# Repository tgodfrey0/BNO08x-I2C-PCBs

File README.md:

# BNO085 Interface Boards (I2C)

This repository contains W.I.P. code and hardware designed for a 9DOF sensor module using a BNO085.

The [`hardware` folder](hardware/README.md) contains all KiCAD files for the board.

The [`firmware` folder](firmware/README.md) contains the files required to run the sensor.

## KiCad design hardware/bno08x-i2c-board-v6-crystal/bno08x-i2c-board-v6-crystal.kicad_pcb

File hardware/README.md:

# Hardware

The PCB designs were created in KiCAD and the panels were made using KiKit.

The sensor board is designed to be as small as possible, for this reason some features of the BNO085 are no longer accessible.

## PCB Board Key

Some of the boards are keyed to give them a known orientation. 

Both keys was created from the insersection between the main PCB edge circle and another circle placed in the top right corner of the main circle's bounding box. They are outlined below in the relevant screenshots (the y-axis has been inverted in Geogebra to visually match the KiCAD coordinate system).

### v6

All v6 boards have the same key and same key location. This is a through-hole with a diameter of 1mm. The centre of the key hole is located in the top left corner of the board; -3.35mm from the centre of the board along the x-axis, -3.25mm from the centre of the board along the y-axis. For both board sizes the hole is located in the same place. (Remember the KiCAD y-axis is inverted, therefore the delta-y of -3.25 means the hole is above the centre of the board.) 

### v5

The v5 board design has no physical key, however orientation pads were added to the front and back silkscreen these are in the top-left, top-right and bottom-right corners and can be used to orientate the board.

### v3

### v3-base

This board is the base for the `v3` panel. The difference is the flat spots by each pin to allow it to be panelised. This means the dimensions are slightly different.

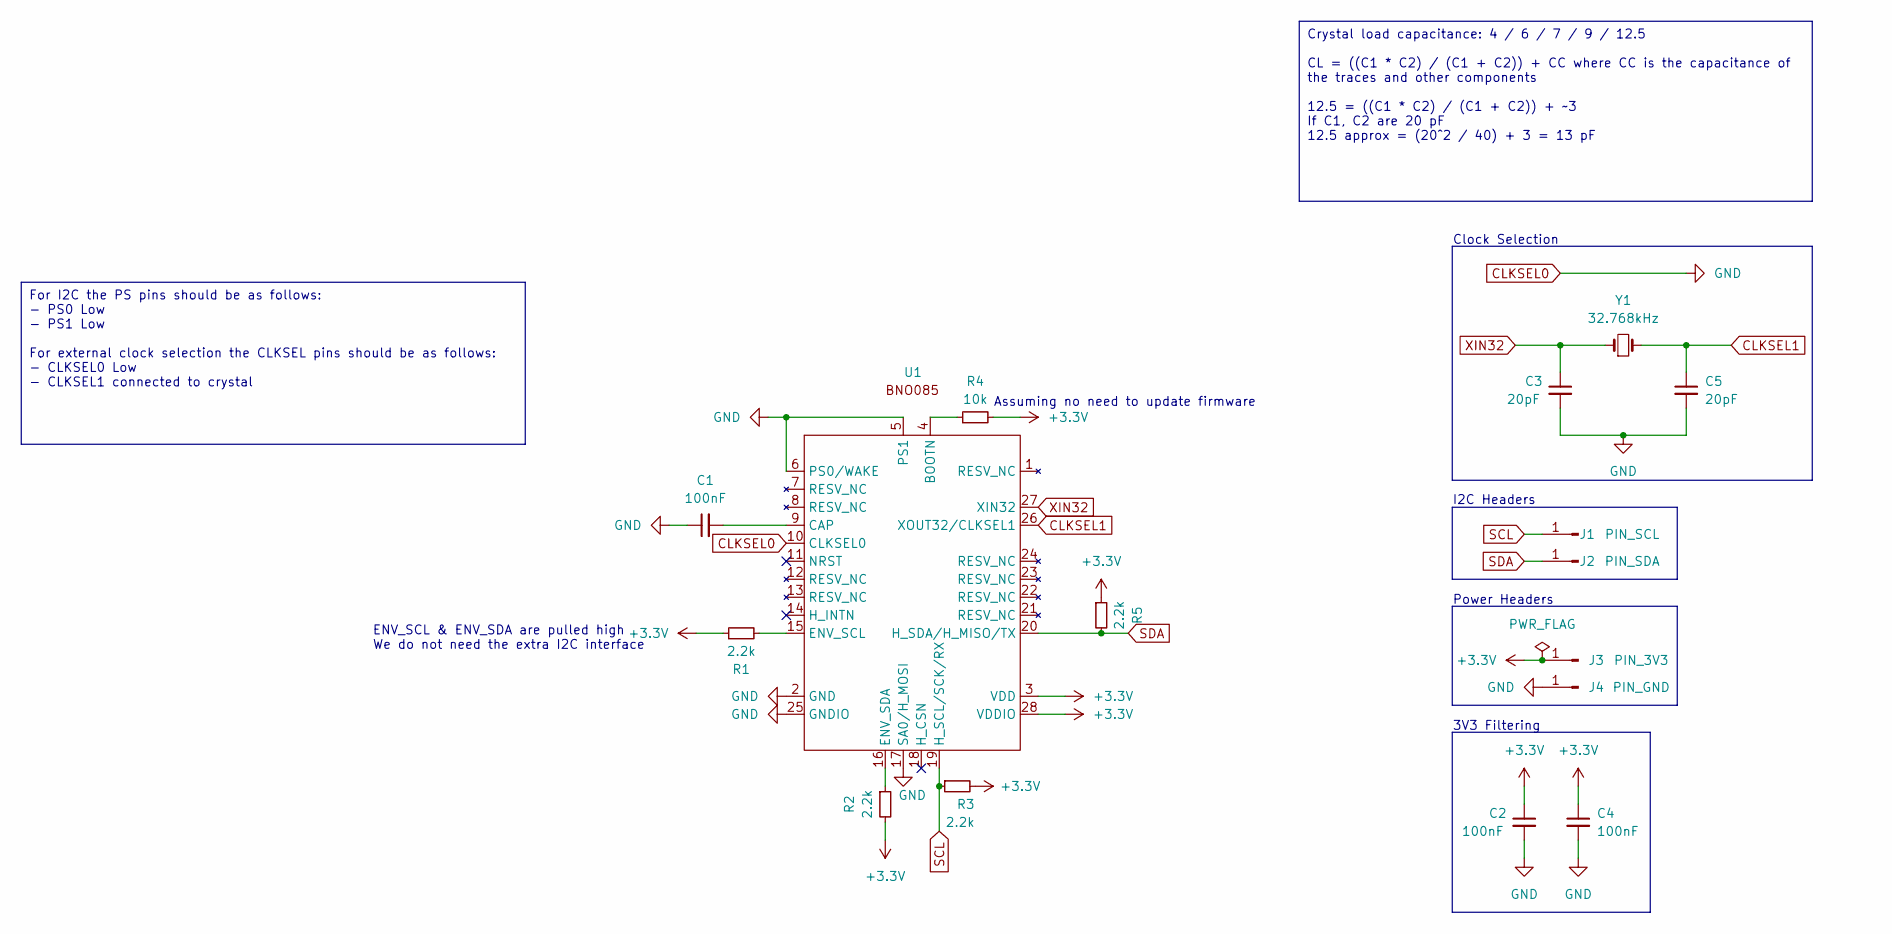
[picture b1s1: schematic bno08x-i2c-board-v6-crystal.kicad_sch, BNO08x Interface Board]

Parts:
C1, C2, C4: 100nF; C_0402_1005Metric
C3, C5: 20pF; C_0402_1005Metric
J1: PIN_SCL; PinHeader_1x01_P1.00mm_Vertical
J2: PIN_SDA; PinHeader_1x01_P1.00mm_Vertical
J3: PIN_3V3; PinHeader_1x01_P1.00mm_Vertical
J4: PIN_GND; PinHeader_1x01_P1.00mm_Vertical
R1, R2, R3, R5: 2.2k; R_0402_1005Metric
R4: 10k; R_0402_1005Metric
U1: LGA-28_5.2x3.8mm_P0.5mm
Y1: 32.768kHz; Crystal_SMD_MicroCrystal_CM9V-T1A-2Pin_1.6x1.0mm

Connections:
+3.3V: C2.1, C4.1, J3.1, R1.1, R2.2, R3.2, R4.2, R5.1, U1.3 (VDD), U1.28 (VDDIO)
CLKSEL0: C1.1, C2.2, C3.2, C4.2, C5.2, J4.1, U1.2 (GND), U1.5 (PS1), U1.6 (PS0/WAKE), U1.10 (CLKSEL0), U1.17 (SA0/H_MOSI), U1.25 (GNDIO)
CLKSEL1: C5.1, U1.26 (XOUT32/CLKSEL1), Y1.2
unnamed: R4.1, U1.4 (BOOTN)
unnamed: C1.2, U1.9 (CAP)
unnamed: R1.2, U1.15 (ENV_SCL)
unnamed: R2.1, U1.16 (ENV_SDA)
SCL: J1.1, R3.1, U1.19 (H_SCL/SCK/RX)
SDA: J2.1, R5.2, U1.20 (H_SDA/H_MISO/TX)
XIN32: C3.1, U1.27 (XIN32), Y1.1

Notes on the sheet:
Crystal load capacitance: 4 / 6 / 7 / 9 / 12.5 CL = ((C1 * C2) / (C1 + C2)) + CC where CC is the capacitance of the traces and other components 12.5 = ((C1 * C2) / (C1 + C2)) + ~3 If C1, C2 are 20 pF 12.5 approx = (20^2 / 40) + 3 = 13 pF
For I2C the PS pins should be as follows: - PS0 Low - PS1 Low For external clock selection the CLKSEL pins should be as follows: - CLKSEL0 Low - CLKSEL1 connected to crystal
3V3 Filtering
Assuming no need to update firmware
Clock Selection
I2C Headers
ENV_SCL & ENV_SDA are pulled high We do not need the extra I2C interface
Power Headers

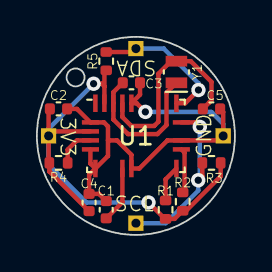
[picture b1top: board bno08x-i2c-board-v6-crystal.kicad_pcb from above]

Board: 2 copper layers, 11.0 x 11.0 mm, 16 parts (0 on the bottom side), 10 nets.

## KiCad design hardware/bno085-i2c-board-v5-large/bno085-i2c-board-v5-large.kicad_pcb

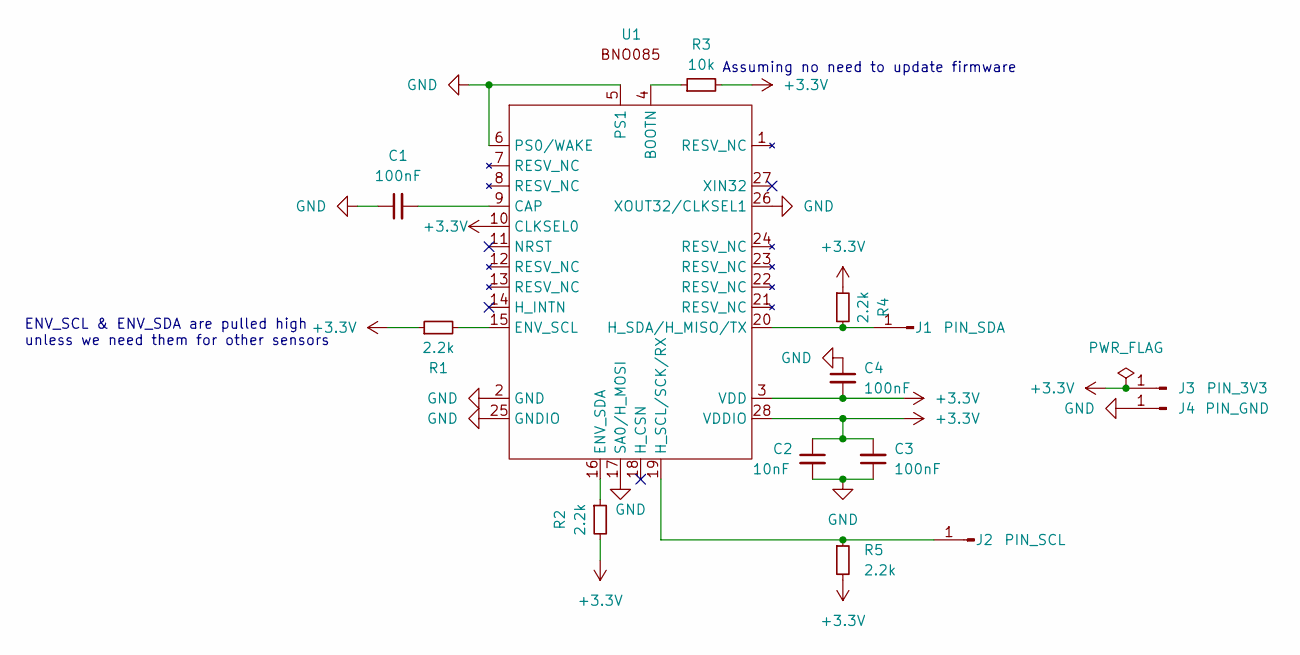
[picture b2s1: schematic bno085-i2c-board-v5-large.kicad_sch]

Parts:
C1, C3, C4: 100nF; C_0402_1005Metric
C2: 10nF; C_0402_1005Metric
J1: PIN_SDA; PinHeader_1x01_P1.00mm_Vertical
J2: PIN_SCL; PinHeader_1x01_P1.00mm_Vertical
J3: PIN_3V3; PinHeader_1x01_P1.00mm_Vertical
J4: PIN_GND; PinHeader_1x01_P1.00mm_Vertical
R1, R2, R4, R5: 2.2k; R_0402_1005Metric
R3: 10k; R_0402_1005Metric
U1: LGA-28_5.2x3.8mm_P0.5mm

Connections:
+3.3V: C2.1, C3.2, C4.2, J3.1, R1.1, R2.2, R3.2, R4.1, R5.2, U1.3 (VDD), U1.10 (CLKSEL0), U1.28 (VDDIO)
GND: C1.1, C2.2, C3.1, C4.1, J4.1, U1.2 (GND), U1.5 (PS1), U1.6 (PS0/WAKE), U1.17 (SA0/H_MOSI), U1.25 (GNDIO), U1.26 (XOUT32/CLKSEL1)
unnamed: J1.1, R4.2, U1.20 (H_SDA/H_MISO/TX)
unnamed: J2.1, R5.1, U1.19 (H_SCL/SCK/RX)
unnamed: R3.1, U1.4 (BOOTN)
unnamed: C1.2, U1.9 (CAP)
unnamed: R1.2, U1.15 (ENV_SCL)
unnamed: R2.1, U1.16 (ENV_SDA)

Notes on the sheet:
Assuming no need to update firmware
ENV_SCL & ENV_SDA are pulled high unless we need them for other sensors

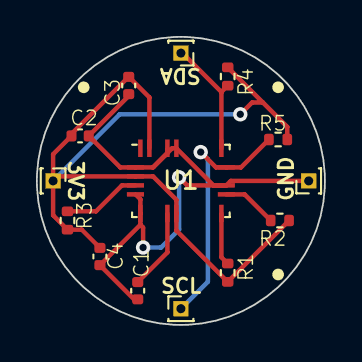
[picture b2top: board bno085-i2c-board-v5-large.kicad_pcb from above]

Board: 2 copper layers, 16.0 x 16.0 mm, 14 parts (0 on the bottom side), 8 nets.

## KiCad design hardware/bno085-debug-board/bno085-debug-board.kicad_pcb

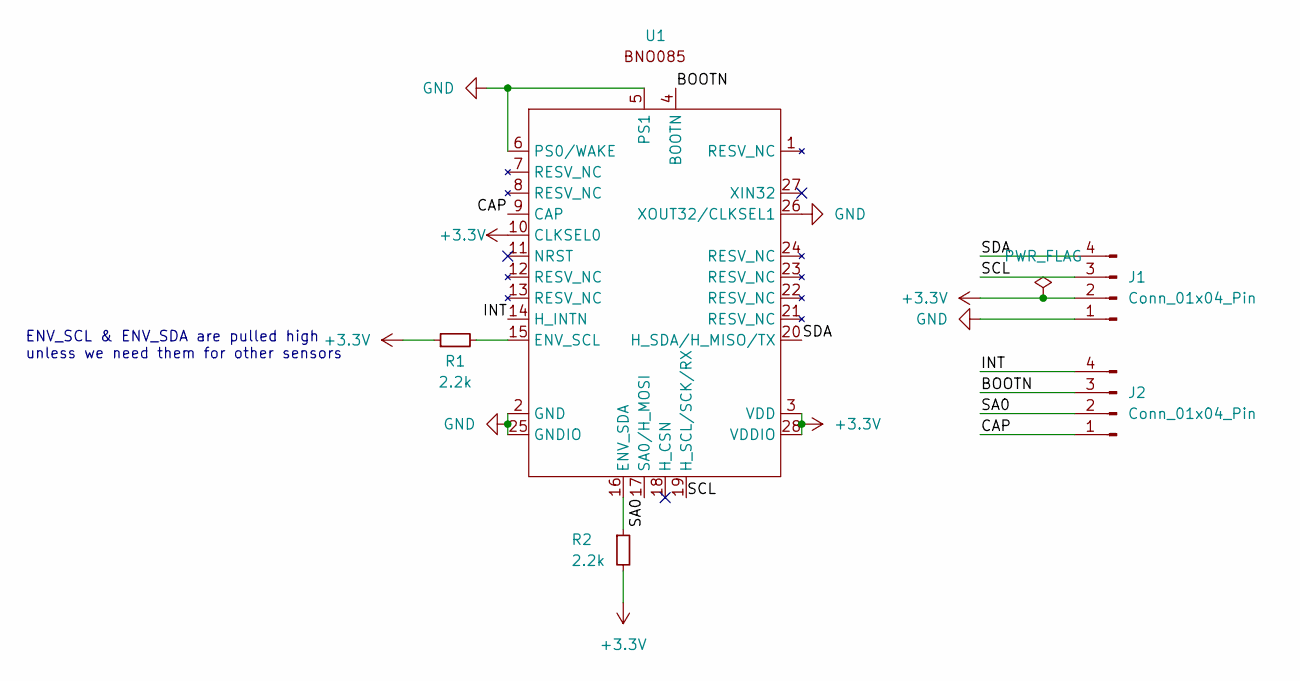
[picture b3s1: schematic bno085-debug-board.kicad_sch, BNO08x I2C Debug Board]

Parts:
J1, J2: Conn_01x04_Pin; PinHeader_1x04_P2.54mm_Vertical
R1, R2: 2.2k; R_Axial_DIN0309_L9.0mm_D3.2mm_P12.70mm_Horizontal
U1: LGA-28_5.2x3.8mm_P0.5mm

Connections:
+3.3V: J1.2, R1.1, R2.2, U1.3 (VDD), U1.10 (CLKSEL0), U1.28 (VDDIO)
/BOOTN: J2.3, U1.4 (BOOTN)
/CAP: J2.1, U1.9 (CAP)
/INT: J2.4, U1.14 (H_INTN)
/SA0: J2.2, U1.17 (SA0/H_MOSI)
/SCL: J1.3, U1.19 (H_SCL/SCK/RX)
/SDA: J1.4, U1.20 (H_SDA/H_MISO/TX)
GND: J1.1, U1.2 (GND), U1.5 (PS1), U1.6 (PS0/WAKE), U1.25 (GNDIO), U1.26 (XOUT32/CLKSEL1)
unnamed: R1.2, U1.15 (ENV_SCL)
unnamed: R2.1, U1.16 (ENV_SDA)

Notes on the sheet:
ENV_SCL & ENV_SDA are pulled high unless we need them for other sensors

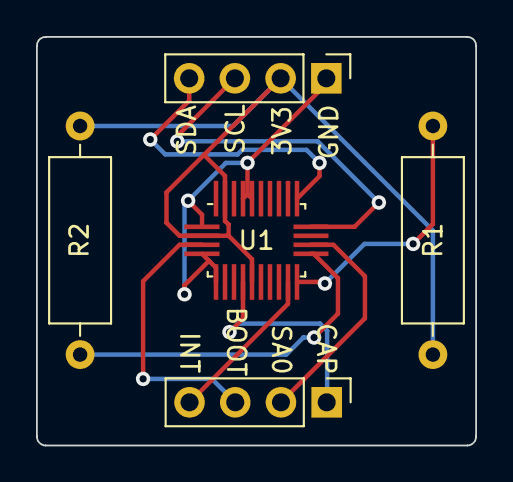
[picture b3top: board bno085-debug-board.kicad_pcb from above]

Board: 2 copper layers, 24.4 x 22.7 mm, 5 parts (0 on the bottom side), 10 nets.

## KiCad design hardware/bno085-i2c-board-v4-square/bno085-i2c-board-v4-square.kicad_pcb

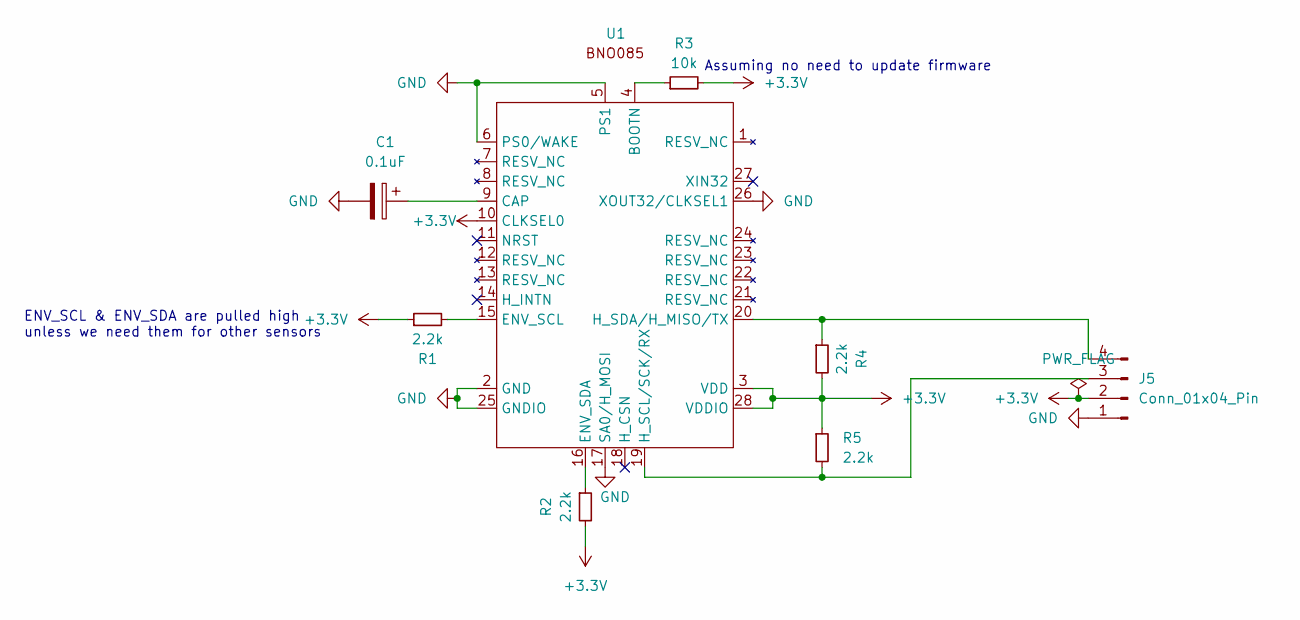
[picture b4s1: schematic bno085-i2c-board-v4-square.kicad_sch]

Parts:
C1: 0.1uF; C_0402_1005Metric
J5: Conn_01x04_Pin; PinHeader_1x04_P2.54mm_Vertical
R1, R2, R4, R5: 2.2k; R_0402_1005Metric
R3: 10k; R_0402_1005Metric
U1: LGA-28_5.2x3.8mm_P0.5mm

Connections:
+3.3V: J5.2, R1.1, R2.2, R3.2, R4.2, R5.1, U1.3 (VDD), U1.10 (CLKSEL0), U1.28 (VDDIO)
GND: C1.2, J5.1, U1.2 (GND), U1.5 (PS1), U1.6 (PS0/WAKE), U1.17 (SA0/H_MOSI), U1.25 (GNDIO), U1.26 (XOUT32/CLKSEL1)
unnamed: J5.3, R5.2, U1.19 (H_SCL/SCK/RX)
unnamed: J5.4, R4.1, U1.20 (H_SDA/H_MISO/TX)
unnamed: R3.1, U1.4 (BOOTN)
unnamed: C1.1, U1.9 (CAP)
unnamed: R1.2, U1.15 (ENV_SCL)
unnamed: R2.1, U1.16 (ENV_SDA)

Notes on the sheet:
Assuming no need to update firmware
ENV_SCL & ENV_SDA are pulled high unless we need them for other sensors

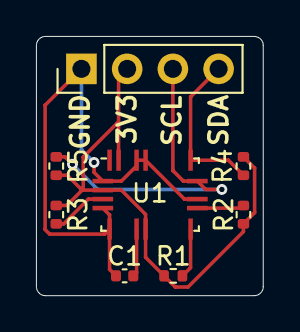
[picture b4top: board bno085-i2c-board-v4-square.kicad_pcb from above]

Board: 2 copper layers, 12.6 x 14.4 mm, 8 parts (0 on the bottom side), 8 nets.

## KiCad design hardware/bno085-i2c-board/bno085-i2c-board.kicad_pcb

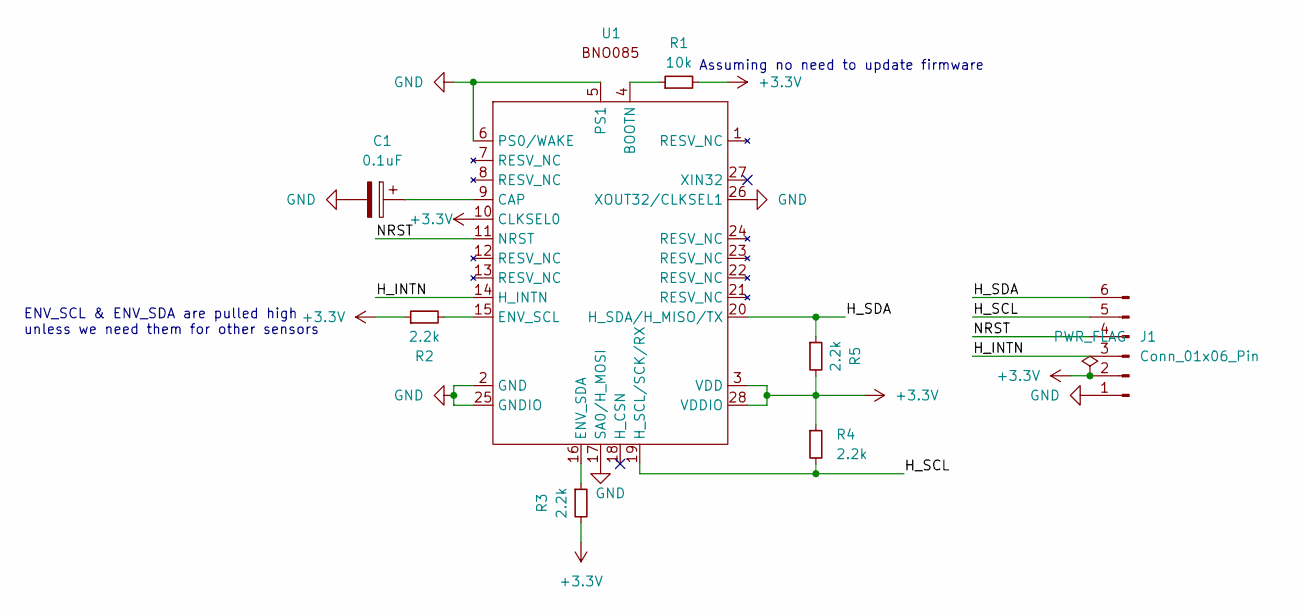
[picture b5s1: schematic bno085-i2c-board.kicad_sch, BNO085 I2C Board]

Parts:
C1: 0.1uF; CP_Radial_D5.0mm_P2.00mm
J1: Conn_01x06_Pin; PinHeader_1x06_P2.54mm_Horizontal
R1: 10k; R_0805_2012Metric
R2, R3, R4, R5: 2.2k; R_0805_2012Metric
U1: LGA-28_5.2x3.8mm_P0.5mm

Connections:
+3.3V: J1.2, R1.2, R2.1, R3.2, R4.1, R5.2, U1.3 (VDD), U1.10 (CLKSEL0), U1.28 (VDDIO)
/H_INTN: J1.3, U1.14 (H_INTN)
/H_SCL: J1.5, R4.2, U1.19 (H_SCL/SCK/RX)
/H_SDA: J1.6, R5.1, U1.20 (H_SDA/H_MISO/TX)
/NRST: J1.4, U1.11 (NRST)
GND: C1.2, J1.1, U1.2 (GND), U1.5 (PS1), U1.6 (PS0/WAKE), U1.17 (SA0/H_MOSI), U1.25 (GNDIO), U1.26 (XOUT32/CLKSEL1)
unnamed: R1.1, U1.4 (BOOTN)
unnamed: C1.1, U1.9 (CAP)
unnamed: R2.2, U1.15 (ENV_SCL)
unnamed: R3.1, U1.16 (ENV_SDA)

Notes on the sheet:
Assuming no need to update firmware
ENV_SCL & ENV_SDA are pulled high unless we need them for other sensors

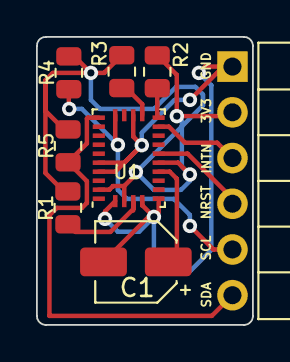
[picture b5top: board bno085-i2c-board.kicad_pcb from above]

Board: 2 copper layers, 12.0 x 16.0 mm, 8 parts (0 on the bottom side), 10 nets.

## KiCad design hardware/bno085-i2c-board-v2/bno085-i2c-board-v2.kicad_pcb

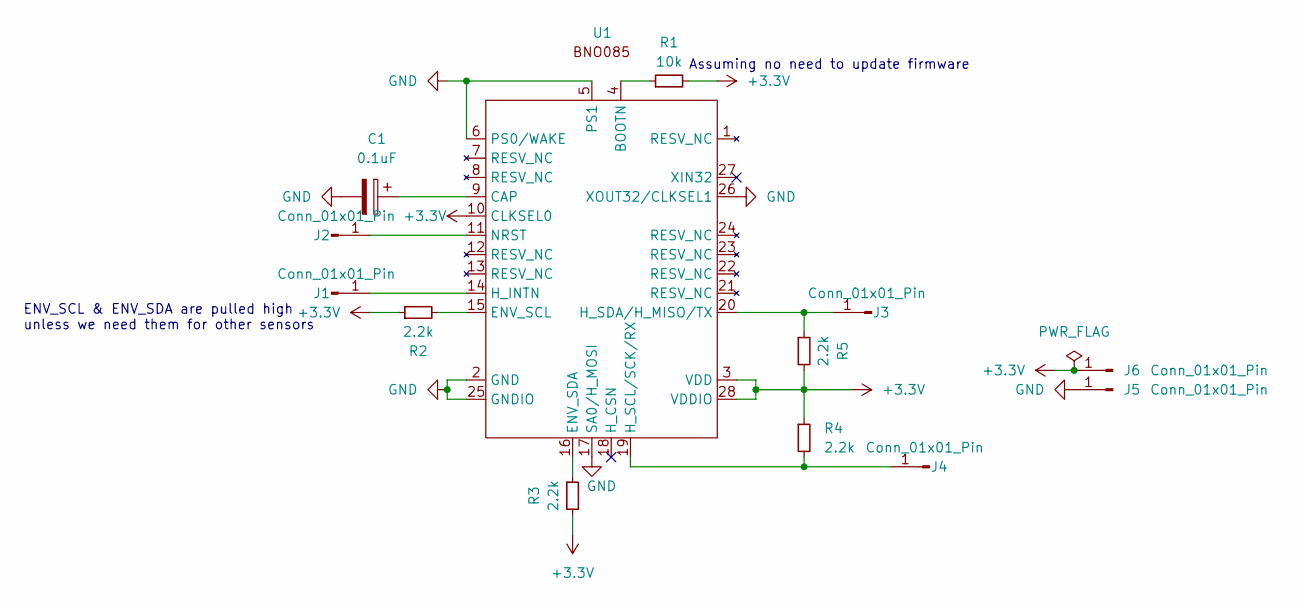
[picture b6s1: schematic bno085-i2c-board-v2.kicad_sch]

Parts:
C1: 0.1uF; C_0402_1005Metric
J1, J2, J3, J4, J5, J6: Conn_01x01_Pin; PinHeader_1x01_P2.54mm_Vertical
R1: 10k; R_0402_1005Metric
R2, R3, R4, R5: 2.2k; R_0402_1005Metric
U1: LGA-28_5.2x3.8mm_P0.5mm

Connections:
+3.3V: J6.1, R1.2, R2.1, R3.2, R4.1, R5.2, U1.3 (VDD), U1.10 (CLKSEL0), U1.28 (VDDIO)
GND: C1.2, J5.1, U1.2 (GND), U1.5 (PS1), U1.6 (PS0/WAKE), U1.17 (SA0/H_MOSI), U1.25 (GNDIO), U1.26 (XOUT32/CLKSEL1)
unnamed: J1.1, U1.14 (H_INTN)
unnamed: J2.1, U1.11 (NRST)
unnamed: J3.1, R5.1, U1.20 (H_SDA/H_MISO/TX)
unnamed: J4.1, R4.2, U1.19 (H_SCL/SCK/RX)
unnamed: R1.1, U1.4 (BOOTN)
unnamed: C1.1, U1.9 (CAP)
unnamed: R2.2, U1.15 (ENV_SCL)
unnamed: R3.1, U1.16 (ENV_SDA)

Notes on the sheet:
Assuming no need to update firmware
ENV_SCL & ENV_SDA are pulled high unless we need them for other sensors

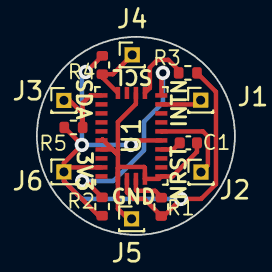
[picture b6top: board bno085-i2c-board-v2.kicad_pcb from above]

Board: 2 copper layers, 11.0 x 11.0 mm, 13 parts (0 on the bottom side), 10 nets.

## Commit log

2023-06-22 started schematic
2023-06-22 more schematic
2023-06-22 schematic
2023-06-22 added pwr flag
2023-06-22 more pcb
2023-06-22 new pcb resistors
2023-06-22 drc checks
2023-06-23 new board
2023-06-23 round board
2023-06-23 firmware folder
2023-06-23 more code
2023-06-23 code
2023-06-26 i2c no work
2023-06-26 holy shit i think it works
2023-06-26 now loops for all reports
2023-06-26 payload size = 0 after 4 reads
2023-06-26 comments
2023-06-26 slight refactor
2023-06-26 idk if this works
2023-06-26 maybe bug gone? moved to timeout when reading header
2023-06-26 smaller max payload size
2023-06-26 i think it does work
2023-06-26 removed debug stuff
2023-06-27 usb debug
2023-06-27 sensor struct
2023-06-27 count reports
2023-06-27 it broken
2023-06-27 still broke
2023-06-27 4 pin board
2023-06-27 moved payload to global
2023-06-27 fixed at last
2023-06-27 metadata
2023-06-27 removed debug prints
2023-06-27 reduced delay
2023-06-27 method sig
2023-06-27 reforamt
2023-06-28 reads product id
2023-06-28 not working
2023-06-28 omg accel works
2023-06-28 i think it works
2023-06-28 cleaned debug messages
2023-06-28 broke
2023-06-28 idk what happened
2023-06-28 added key
2023-06-28 issue from payload -> structs and timing
2023-06-29 so close
2023-06-29 so bloody close
2023-06-29 works for one sensor
2023-06-29 finished
2023-06-29 square board
2023-06-29 units
2023-06-29 signed numbers
2023-06-29 panels
2023-06-30 square panel
2023-06-30 small panels
2023-06-30 panels and board metadata
2023-06-30 readmes
2023-06-30 gitignore and photo
2023-06-30 gitignore
2023-06-30 cleaned
2023-06-30 rename
2023-06-30 license
2023-07-03 somewhat better
2023-07-03 testing stencil generation
2023-07-03 pcbs
2023-07-03 key images
2023-07-04 removed stencils
2023-07-07 readme
2023-07-07 submodule
2023-07-07 jlc fab files
2023-07-07 drill map files
2023-07-07 fab zips
2023-07-07 zips
2023-07-07 moved v3
2023-07-25 boards
2023-07-26 v4-large-panel
2023-07-26 gerbers
2023-07-31 square
2023-08-09 licenses
2023-08-14 debug board
2023-08-18 large
2023-08-21 locks
2023-08-23 change cap size
2023-08-24 v6 crystal
